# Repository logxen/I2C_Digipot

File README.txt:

This is a simple 1 layer breakout board for the MAX5387 dual digipot.

Bill of Materials:

1x - 1.5" x 0.75" single sided copper clad board (pcb)
1x - MAX5387 dual digipot ic, 14 pin tssop (main ic)
1x - 0.1uF tantalum cap, 1206 (power filter)
2x - 4.7kOhm, 1206 (pull-ups for i2c bus)
1x - 1x4 0.1" pin header (i2c bus: vcc, scl, sda, gnd)
2x - 1x5 0.1" pin header (digipot ports: vcc, high, wiper, low, gnd)

NOTES:

- the .png file has descriptive layers, the .bmp is just the b/w copper mask for etching

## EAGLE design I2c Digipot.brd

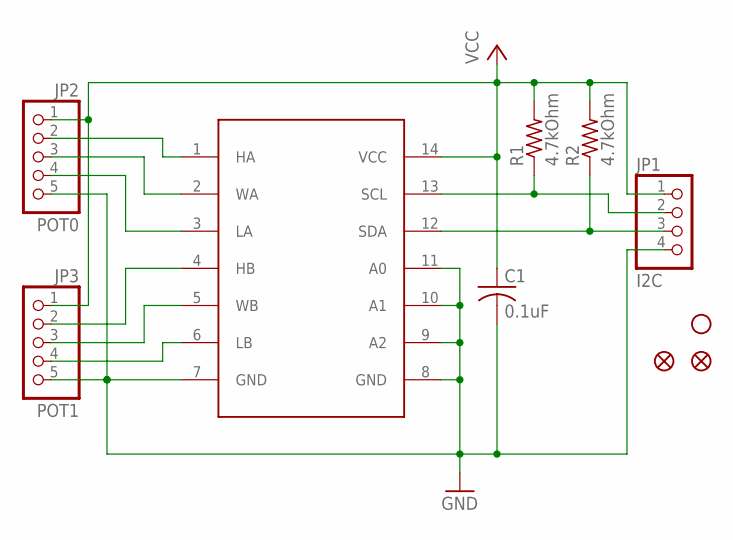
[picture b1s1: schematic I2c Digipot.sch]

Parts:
C1: 0.1uF; C1206
JP1: I2C; 1X04
JP2: POT0; 1X05
JP3: POT1; 1X05
JP5: STAND-OFF
JP6, JP7: FIDUCIAL1X2; FIDUCIAL-1X2
R1, R2: 4.7kOhm; R1206
U1: MAX5387; TSSOP14

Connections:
GND: C1.2, JP1.4, JP2.5, JP3.5, U1.7 (GND), U1.8 (GND), U1.9 (A2), U1.10 (A1), U1.11 (A0)
HA: JP2.2, U1.1 (HA)
HB: JP3.2, U1.4 (HB)
LA: JP2.4, U1.3 (LA)
LB: JP3.4, U1.6 (LB)
SCL: JP1.2, R1.1, U1.13 (SCL)
SDA: JP1.3, R2.1, U1.12 (SDA)
VCC: C1.1, JP1.1, JP2.1, JP3.1, R1.2, R2.2, U1.14 (VCC)
WA: JP2.3, U1.2 (WA)
WB: JP3.3, U1.5 (WB)

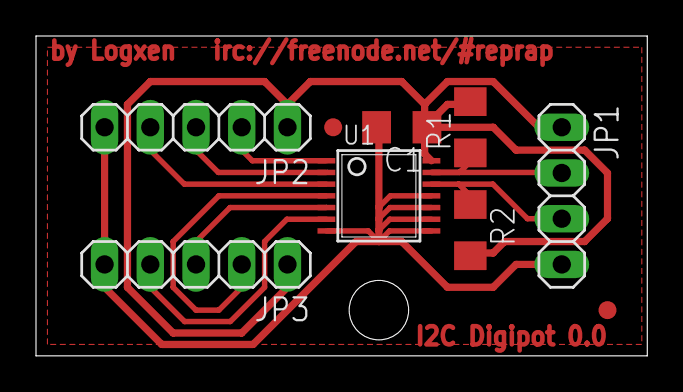
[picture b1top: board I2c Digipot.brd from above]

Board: 2 copper layers, 34.0 x 17.8 mm, 10 parts (0 on the bottom side), 10 nets.

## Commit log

2012-07-05 Rotated i2c pull-up resistors to save 0.1" in y
2012-07-05 rotated pot1 output so it matches pot0
2012-07-05 removed deprecated note about pot1 from readme
2012-07-05 made text thicker

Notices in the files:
parts and their libraries:
SparkFun: Licensing: CC v3.0 Share-Alike You are welcome to use this library for commercial purposes.
